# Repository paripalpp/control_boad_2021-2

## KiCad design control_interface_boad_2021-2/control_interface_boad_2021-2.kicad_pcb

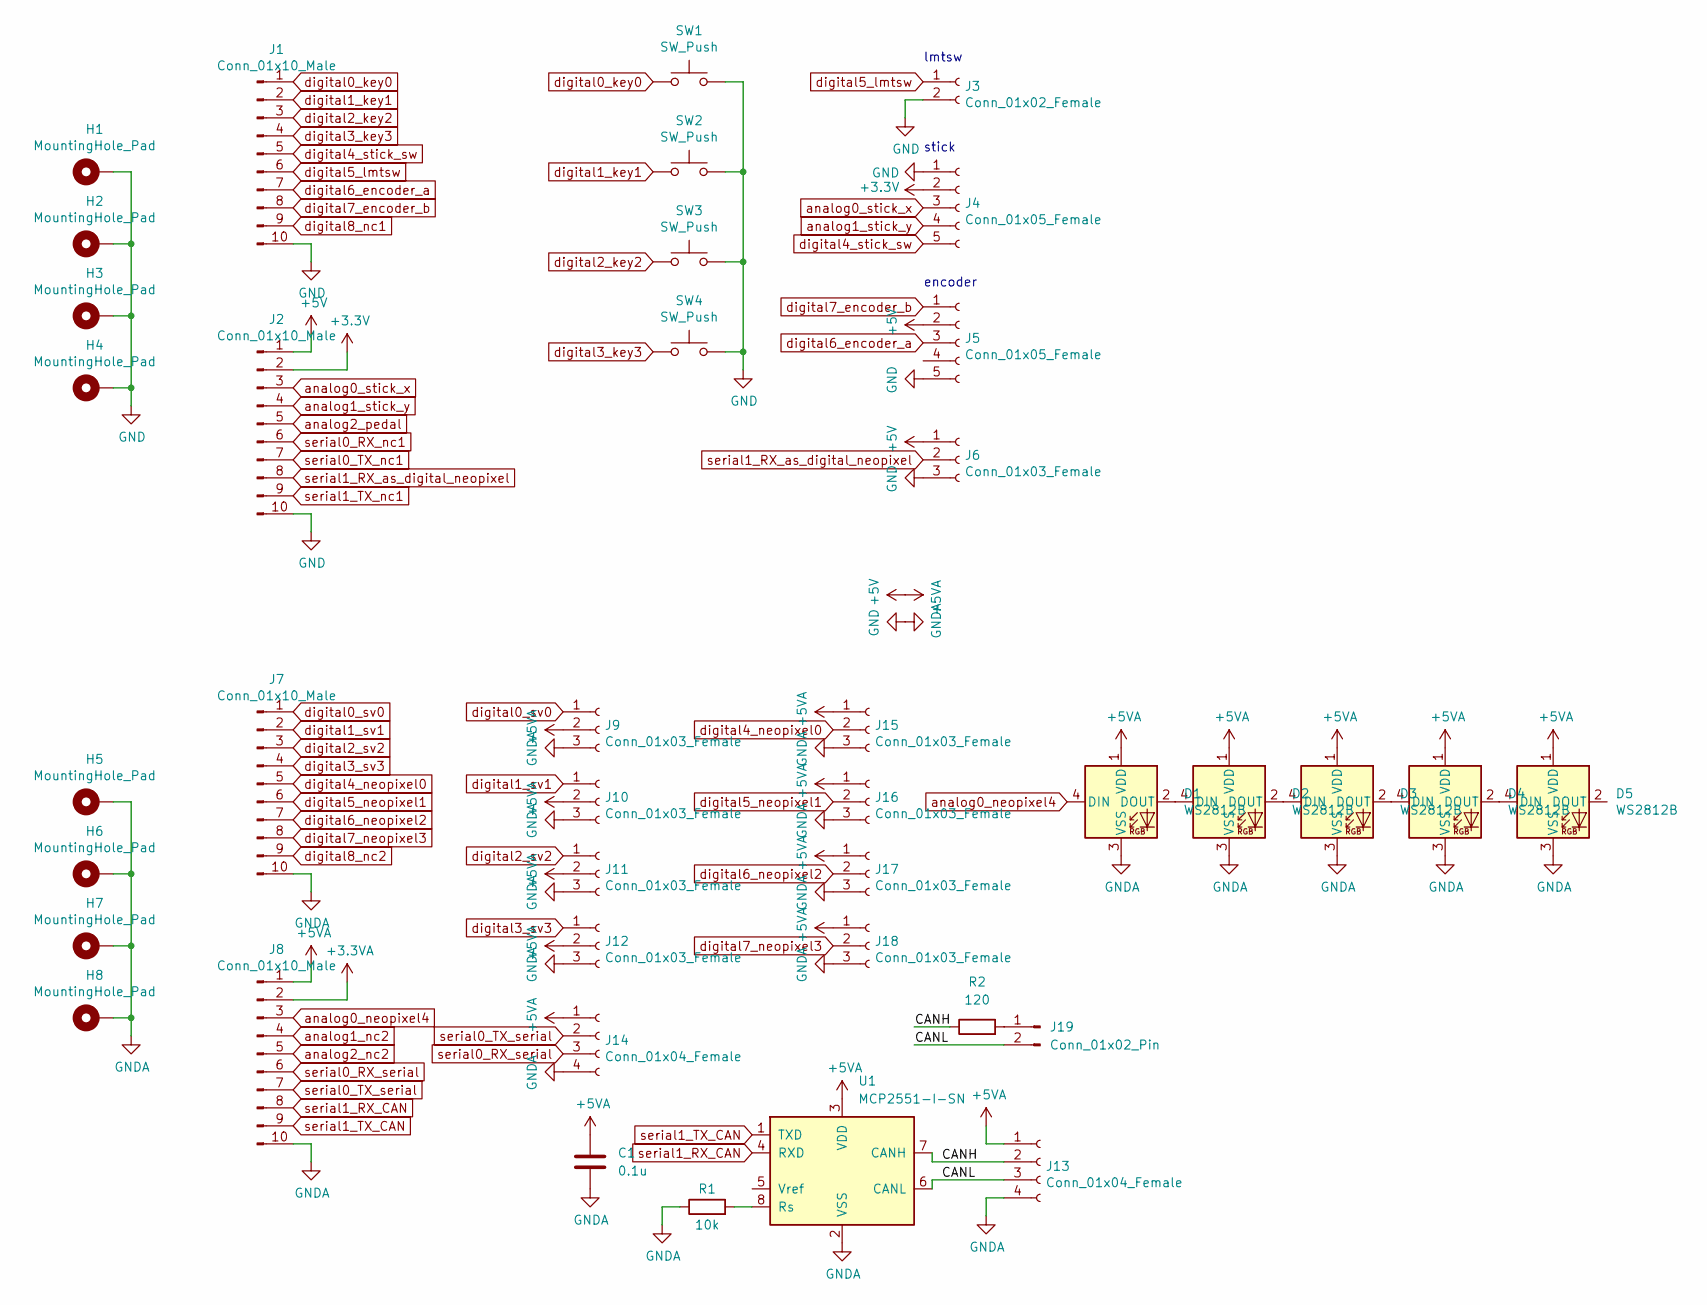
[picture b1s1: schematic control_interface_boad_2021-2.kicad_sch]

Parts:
C1: 0.1u; C_0603_1608Metric
D1, D2, D3, D4, D5: WS2812B; LED_WS2812B_PLCC4_5.0x5.0mm_P3.2mm
H1, H2, H3, H4, H5, H6, H7, H8: MountingHole_Pad; MountingHole_3.2mm_M3_Pad
J1, J2, J7, J8: Conn_01x10_Male; PinHeader_1x10_P2.54mm_Vertical
J3: Conn_01x02_Female; JST_XA_S02B-XASK-1_1x02_P2.50mm_Horizontal
J4, J5: Conn_01x05_Female; JST_XA_S05B-XASK-1_1x05_P2.50mm_Horizontal
J6, J9, J10, J11, J12, J15, J16, J17, J18: Conn_01x03_Female; JST_XA_S03B-XASK-1_1x03_P2.50mm_Horizontal
J13, J14: Conn_01x04_Female; JST_XA_S04B-XASK-1_1x04_P2.50mm_Horizontal
J19: Conn_01x02_Pin; PinHeader_1x02_P2.54mm_Vertical
R1: 10k; R_0603_1608Metric
R2: 120; R_0603_1608Metric
SW1, SW2, SW3, SW4: SW_Push; SW_Cherry_MX_1.25u_PCB
U1: MCP2551-I-SN; SOIC-8_3.9x4.9mm_P1.27mm

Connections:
+3.3VA: J8.2
+3V3: J2.2, J4.2
+5V: C1.1, D1.1 (VDD), D2.1 (VDD), D3.1 (VDD), D4.1 (VDD), D5.1 (VDD), J2.1, J5.2, J6.1, J8.1, J9.2, J10.2, J11.2, J12.2, J13.1, J14.1, J15.1, J16.1, J17.1, J18.1, U1.3 (VDD)
/CANH: J13.2, R2.1, U1.7 (CANH)
/CANL: J13.3, J19.2, U1.6 (CANL)
GND: C1.2, D1.3 (VSS), D2.3 (VSS), D3.3 (VSS), D4.3 (VSS), D5.3 (VSS), H1.1, H2.1, H3.1, H4.1, H5.1, H6.1, H7.1, H8.1, J1.10, J2.10, J3.2, J4.1, J5.5, J6.3, J7.10, J8.10, J9.3, J10.3, J11.3, J12.3, J13.4, J14.4, J15.3, J16.3, J17.3, J18.3, R1.1, SW1.2, SW2.2, SW3.2, SW4.2, U1.2 (VSS)
unnamed: D1.2 (DOUT), D2.4 (DIN)
unnamed: D2.2 (DOUT), D3.4 (DIN)
unnamed: D3.2 (DOUT), D4.4 (DIN)
unnamed: D4.2 (DOUT), D5.4 (DIN)
unnamed: J19.1, R2.2
unnamed: R1.2, U1.8 (Rs)
analog0_neopixel4: D1.4 (DIN), J8.3
analog0_stick_x: J2.3, J4.3
analog1_nc2: J8.4
analog1_stick_y: J2.4, J4.4
analog2_nc2: J8.5
analog2_pedal: J2.5
digital0_key0: J1.1, SW1.1
digital0_sv0: J7.1, J9.1
digital1_key1: J1.2, SW2.1
digital1_sv1: J7.2, J10.1
digital2_key2: J1.3, SW3.1
digital2_sv2: J7.3, J11.1
digital3_key3: J1.4, SW4.1
digital3_sv3: J7.4, J12.1
digital4_neopixel0: J7.5, J15.2
digital4_stick_sw: J1.5, J4.5
digital5_lmtsw: J1.6, J3.1
digital5_neopixel1: J7.6, J16.2
digital6_encoder_a: J1.7, J5.3
digital6_neopixel2: J7.7, J17.2
digital7_encoder_b: J1.8, J5.1
digital7_neopixel3: J7.8, J18.2
digital8_nc1: J1.9
digital8_nc2: J7.9
serial0_RX_nc1: J2.6
serial0_RX_serial: J8.6, J14.3
serial0_TX_nc1: J2.7
serial0_TX_serial: J8.7, J14.2
serial1_RX_CAN: J8.8, U1.4 (RXD)
serial1_RX_as_digital_neopixel: J2.8, J6.2
serial1_TX_CAN: J8.9, U1.1 (TXD)
serial1_TX_nc1: J2.9

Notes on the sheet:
stick
lmtsw
encoder

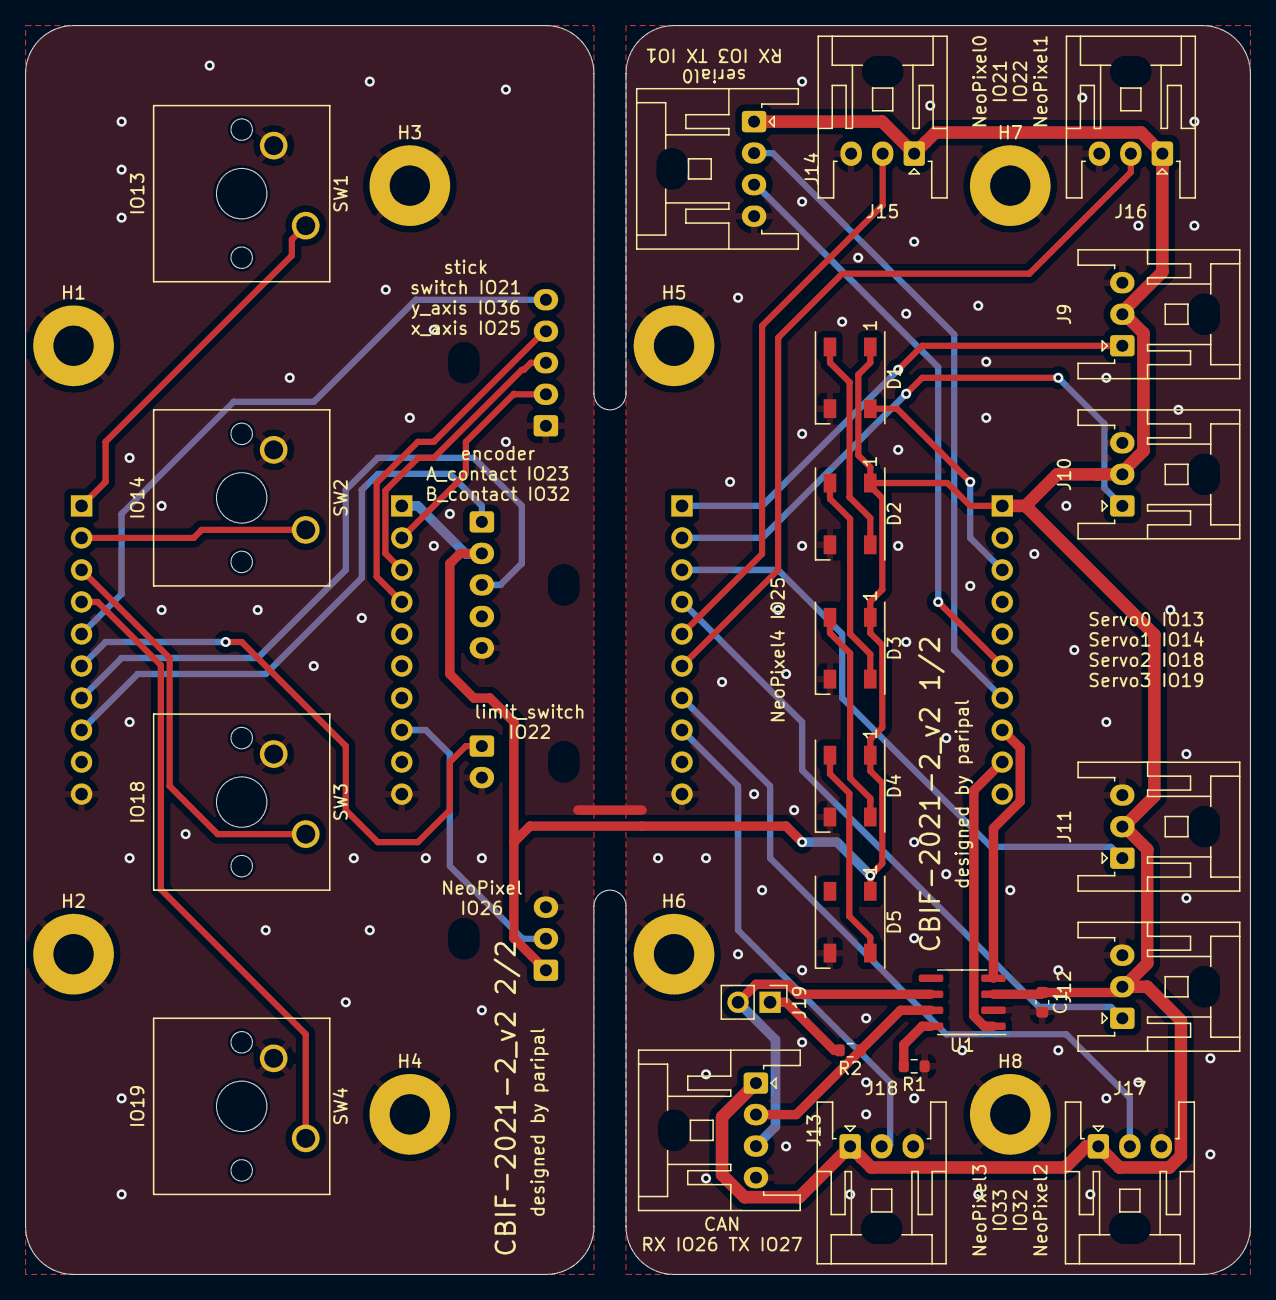
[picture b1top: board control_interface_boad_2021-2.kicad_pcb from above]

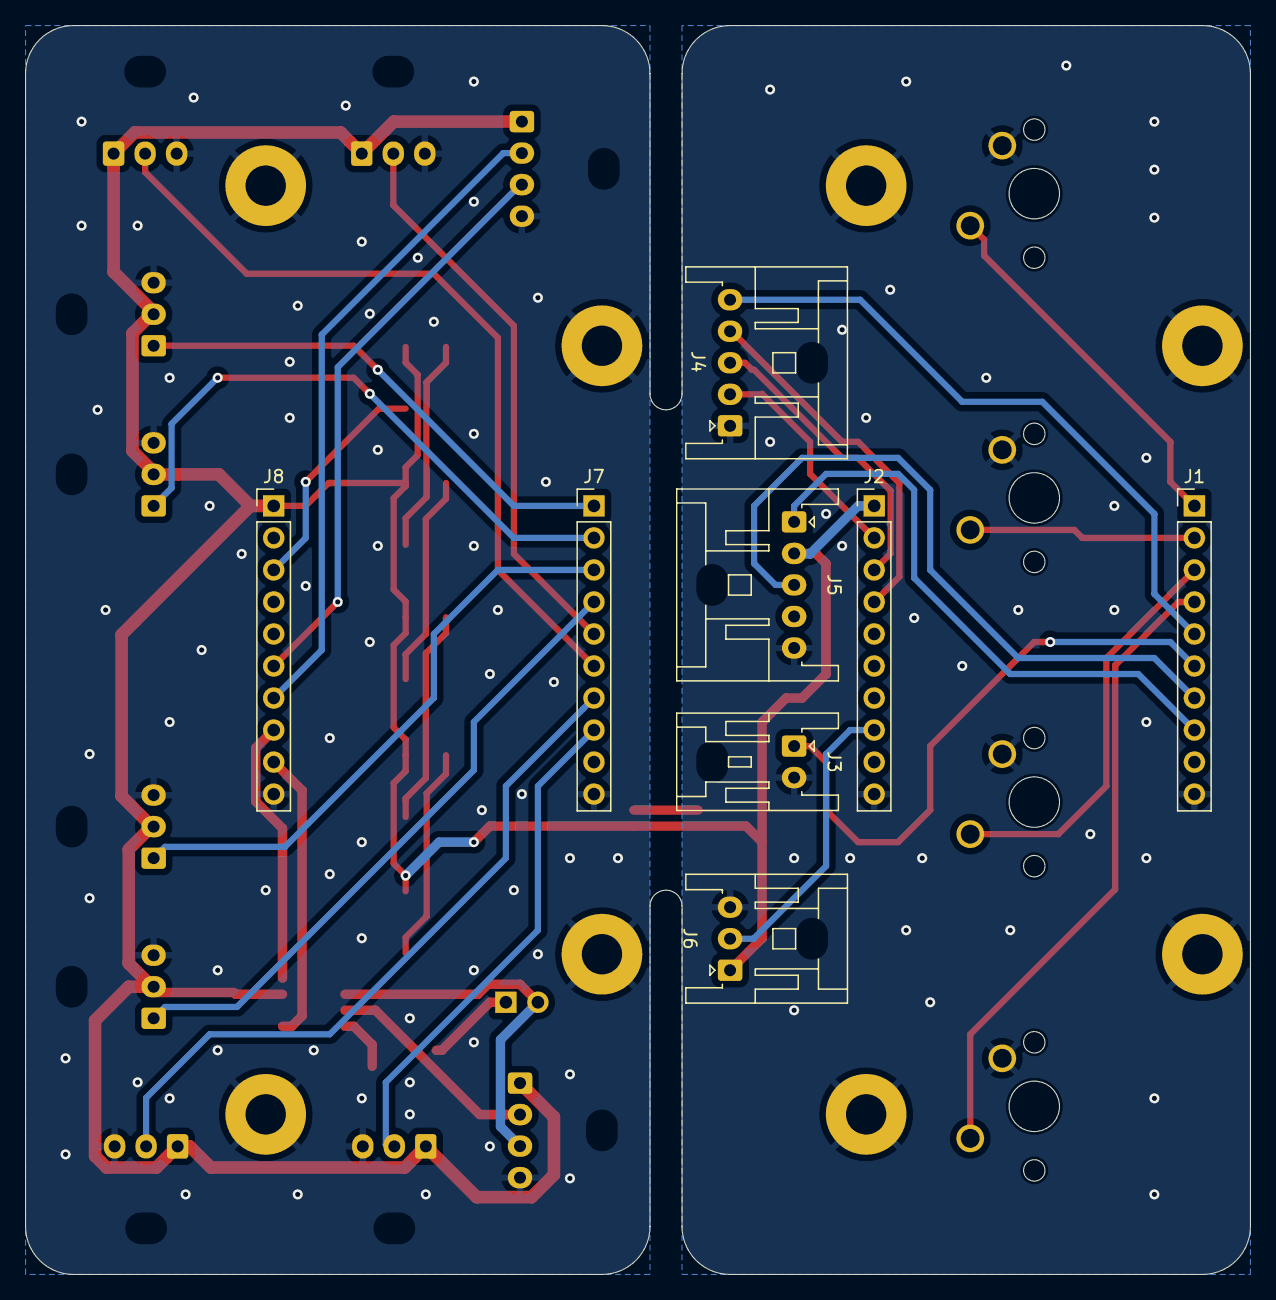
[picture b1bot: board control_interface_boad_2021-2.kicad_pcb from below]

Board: 2 copper layers, 97.2 x 99.1 mm, 40 parts (8 on the bottom side), 35 nets.

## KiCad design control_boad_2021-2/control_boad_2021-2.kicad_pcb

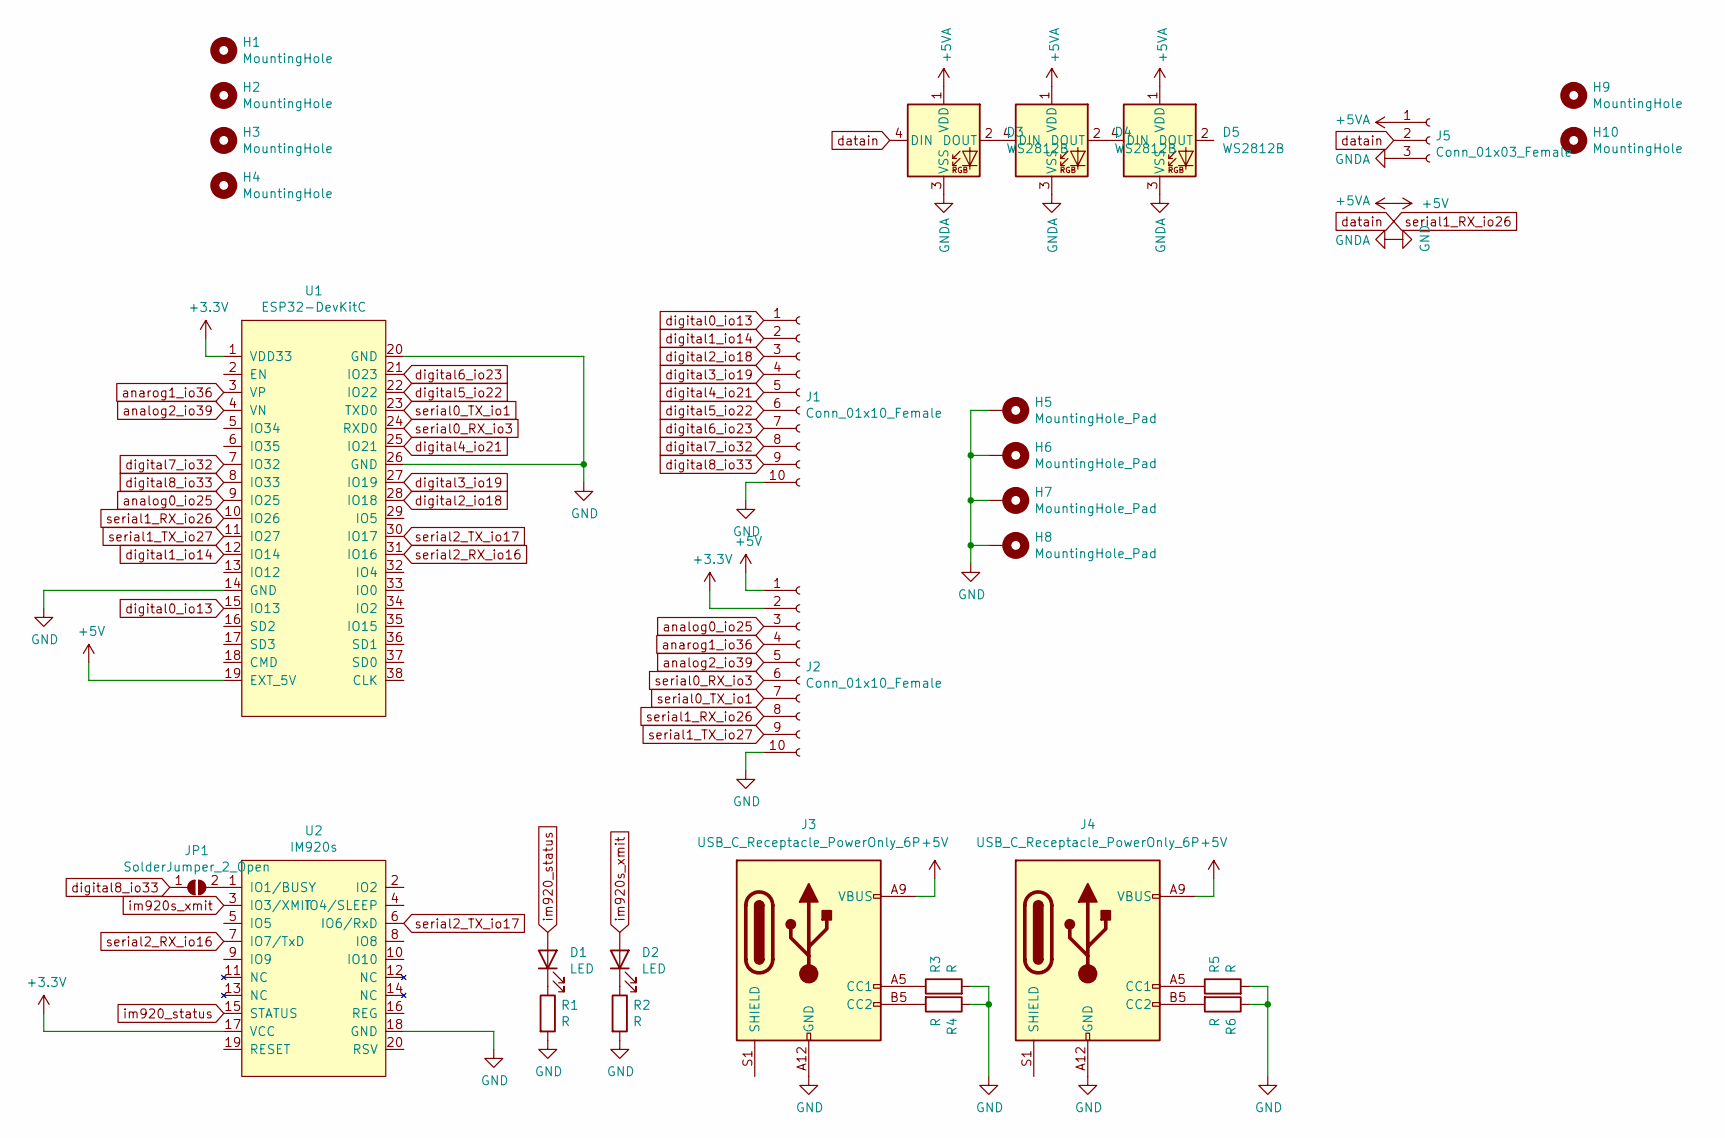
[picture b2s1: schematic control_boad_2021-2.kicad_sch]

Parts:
D1, D2: LED; LED_0603_1608Metric
D3, D4, D5: WS2812B; LED_WS2812B_PLCC4_5.0x5.0mm_P3.2mm
H1, H2, H3, H4: MountingHole; MountingHole_3.2mm_M3_Pad_Via
H5, H6, H7, H8: MountingHole_Pad; MountingHole_3.2mm_M3_Pad
H9, H10: MountingHole; MountingHole_3.2mm_M3_Pad
J1, J2: Conn_01x10_Female; PinSocket_1x10_P2.54mm_Vertical
J3, J4: USB_C_Receptacle_PowerOnly_6P; USB_C_Receptacle_CUI_ UJC-HP-3-SMT-TR_TopMnt_Horizontal
J5: Conn_01x03_Female; JST_XA_B03B-XASK-1_1x03_P2.50mm_Vertical
JP1: SolderJumper_2_Open; SolderJumper-2_P1.3mm_Open_TrianglePad1.0x1.5mm
R1, R2, R3, R4, R5, R6: R; R_0603_1608Metric
U1: ESP32-DevKitC
U2: IM920s

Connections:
+3V3: J2.2, U1.1 (VDD33), U2.17 (VCC)
+5V: D3.1 (VDD), D4.1 (VDD), D5.1 (VDD), J2.1, J3.A9 (VBUS), J3.B9 (VBUS), J4.A9 (VBUS), J4.B9 (VBUS), J5.1, U1.19 (EXT_5V)
GND: D3.3 (VSS), D4.3 (VSS), D5.3 (VSS), H5.1, H6.1, H7.1, H8.1, J1.10, J2.10, J3.A12 (GND), J3.B12 (GND), J4.A12 (GND), J4.B12 (GND), J5.3, R1.2, R2.2, R3.2, R4.1, R5.2, R6.1, U1.14 (GND), U1.20 (GND), U1.26 (GND), U2.18 (GND)
unnamed: D1.1 (K), R1.1
unnamed: D2.1 (K), R2.1
unnamed: D3.2 (DOUT), D4.4 (DIN)
unnamed: D4.2 (DOUT), D5.4 (DIN)
unnamed: J3.A5 (CC1), R3.1
unnamed: J3.B5 (CC2), R4.2
unnamed: J4.A5 (CC1), R5.1
unnamed: J4.B5 (CC2), R6.2
unnamed: JP1.2 (B), U2.1 (IO1/BUSY)
analog0_io25: J2.3, U1.9 (IO25)
analog2_io39: J2.5, U1.4 (VN)
anarog1_io36: J2.4, U1.3 (VP)
datain: D3.4 (DIN), J2.8, J5.2, U1.10 (IO26)
digital0_io13: J1.1, U1.15 (IO13)
digital1_io14: J1.2, U1.12 (IO14)
digital2_io18: J1.3, U1.28 (IO18)
digital3_io19: J1.4, U1.27 (IO19)
digital4_io21: J1.5, U1.25 (IO21)
digital5_io22: J1.6, U1.22 (IO22)
digital6_io23: J1.7, U1.21 (IO23)
digital7_io32: J1.8, U1.7 (IO32)
digital8_io33: J1.9, JP1.1 (A), U1.8 (IO33)
im920_status: D1.2 (A), U2.15 (STATUS)
im920s_xmit: D2.2 (A), U2.3 (IO3/XMIT)
serial0_RX_io3: J2.6, U1.24 (RXD0)
serial0_TX_io1: J2.7, U1.23 (TXD0)
serial1_TX_io27: J2.9, U1.11 (IO27)
serial2_RX_io16: U1.31 (IO16), U2.7 (IO7/TxD)
serial2_TX_io17: U1.30 (IO17), U2.6 (IO6/RxD)

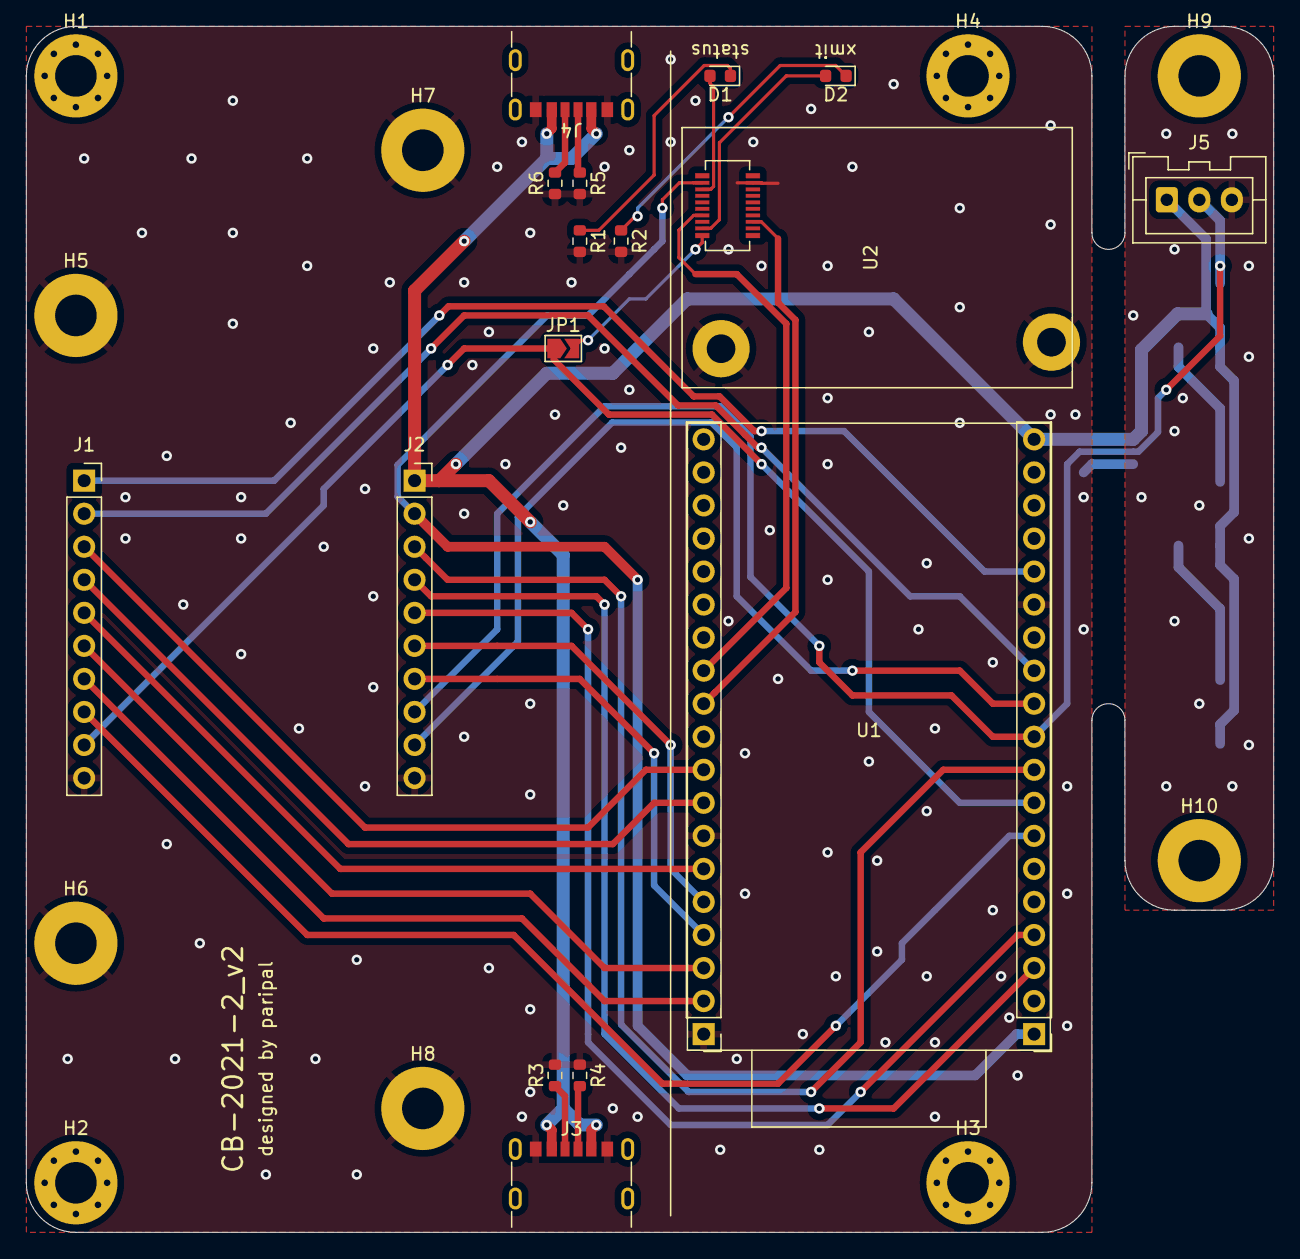
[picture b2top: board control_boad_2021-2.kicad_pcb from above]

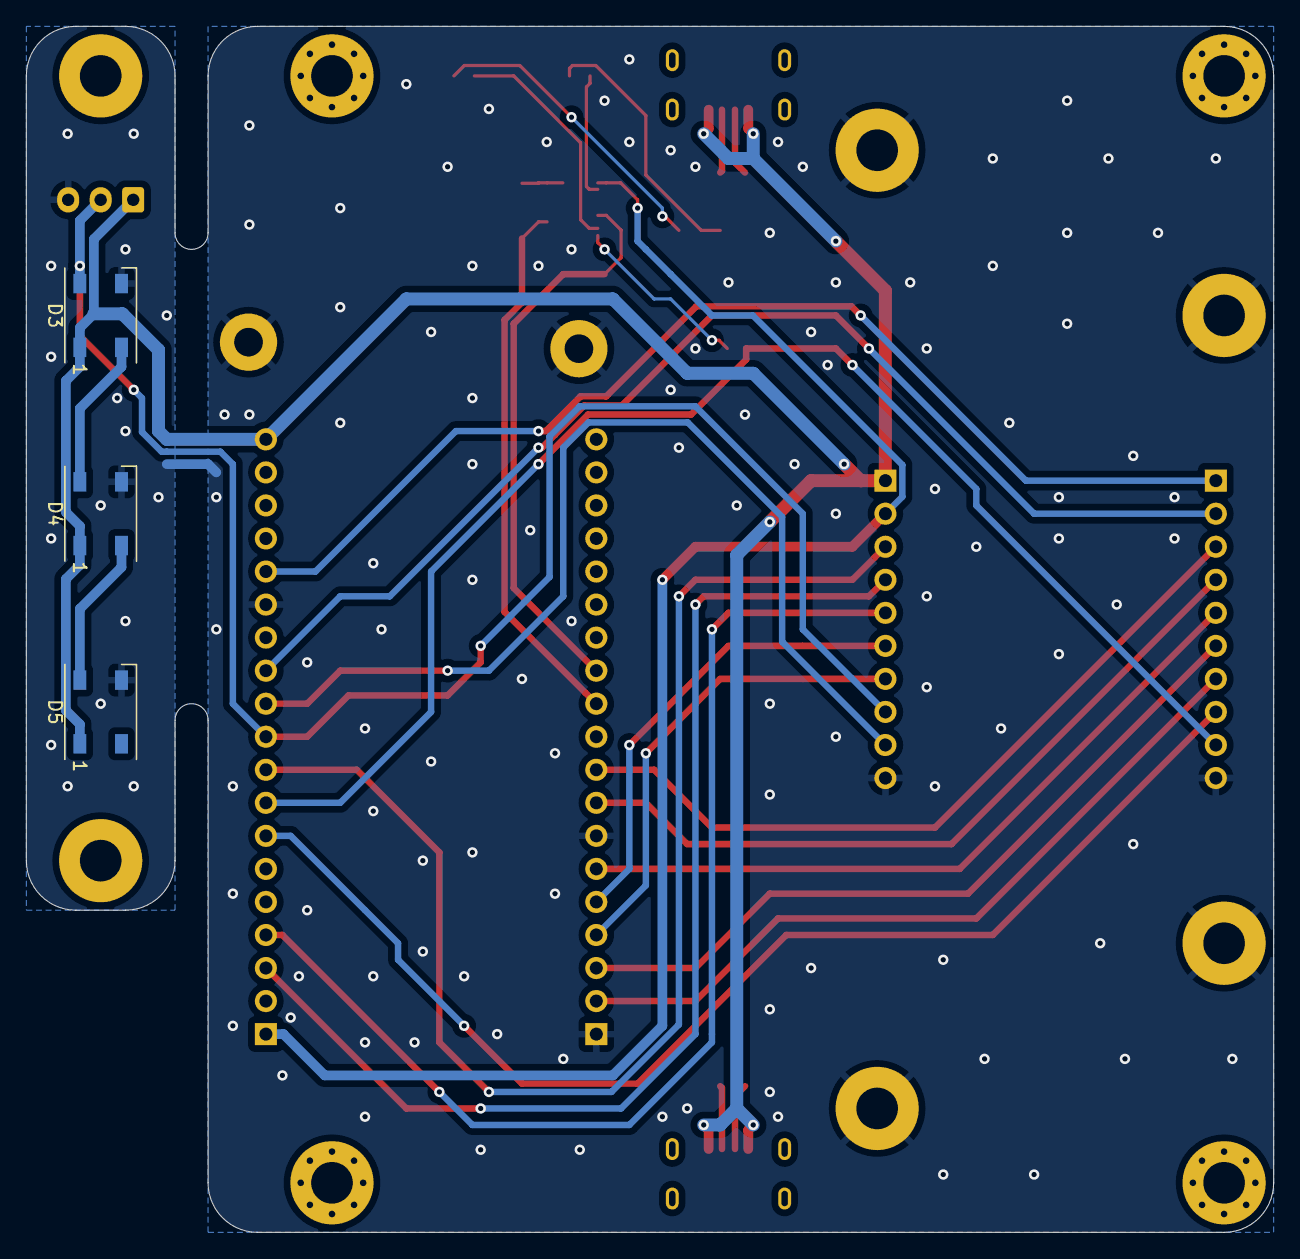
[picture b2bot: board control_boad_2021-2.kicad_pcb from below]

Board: 2 copper layers, 95.9 x 92.7 mm, 29 parts (3 on the bottom side), 32 nets.

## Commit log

2021-11-02 complete!!!
2021-11-03 added gbr files
2021-11-08 added 3d file and pdf file
2023-10-02 v2 comp
2023-10-03 replace esp32devkitc to doit esp32devkit v1
